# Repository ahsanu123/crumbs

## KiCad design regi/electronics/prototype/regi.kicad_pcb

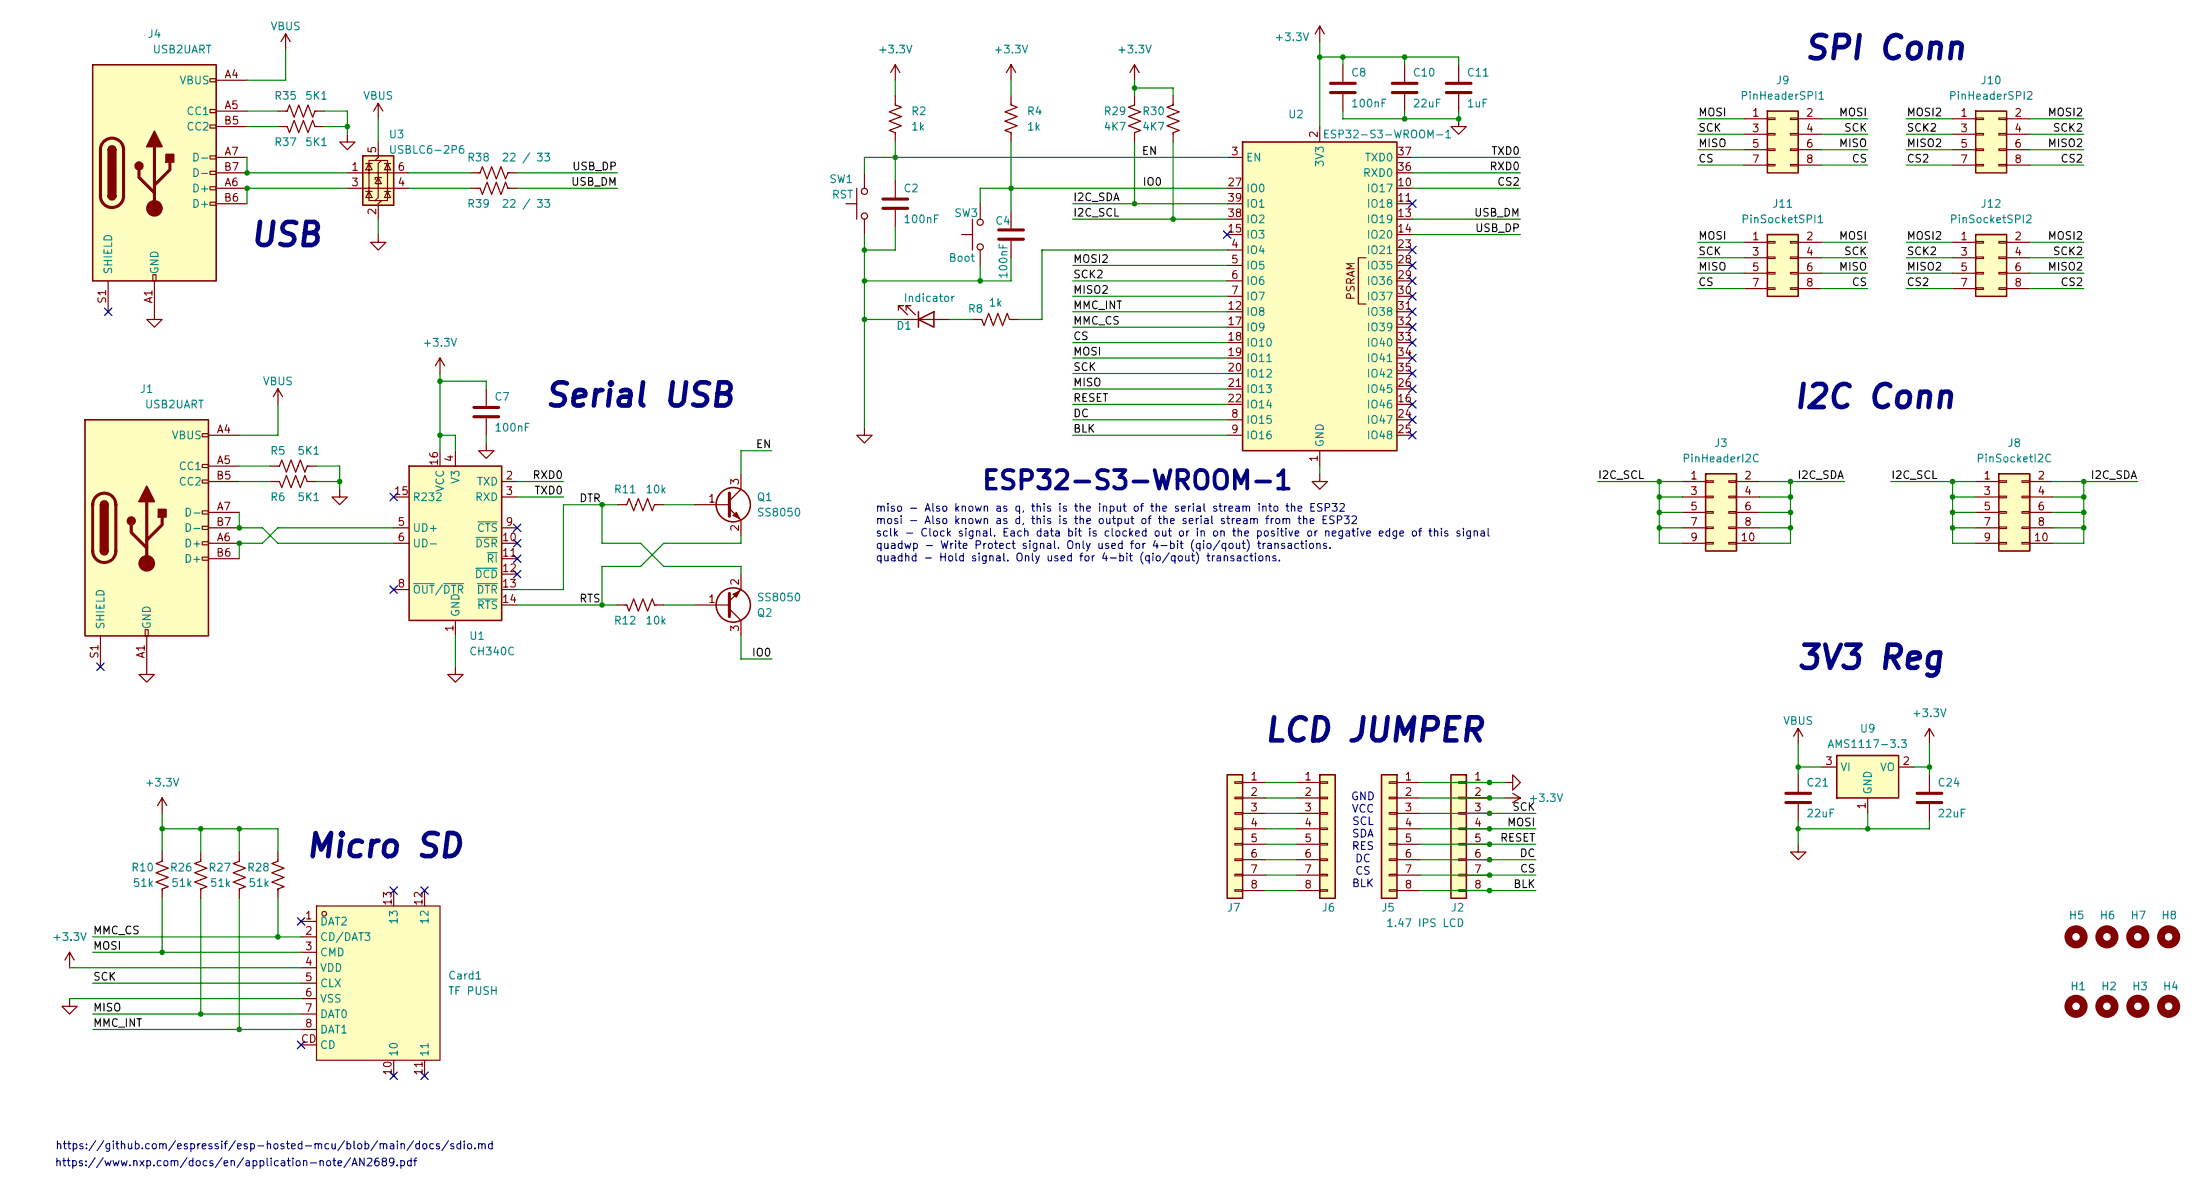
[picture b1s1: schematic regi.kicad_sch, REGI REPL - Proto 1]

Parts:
C2, C4, C7, C8: 100nF; C_0805_2012Metric_Pad1.18x1.45mm_HandSolder
C10, C21, C24: 22uF; C_0805_2012Metric_Pad1.18x1.45mm_HandSolder
C11: 1uF; C_0805_2012Metric_Pad1.18x1.45mm_HandSolder
Card1: TF PUSH; TF-SMD_TF-PUSH; MPN TF PUSH; LCSC Part C393941
D1: Indicator; LED_1206_3216Metric_Pad1.42x1.75mm_HandSolder
H1, H2, H3, H4: MountingHole; MountingHole_2mm
H5, H6, H7, H8: MountingHole; MountingHole_3.2mm_M3
J1, J4: USB2UART; USB_C_Receptacle_GCT_USB4110
J2: 1.47 IPS LCD; PinHeader_1x08_P2.54mm_Vertical
J3: PinHeaderI2C; PinHeader_2x05_P2.54mm_Vertical
J5, J6, J7: lcd jumper; PinHeader_1x08_P2.54mm_Vertical
J8: PinSocketI2C; PinSocket_2x05_P2.54mm_Vertical
J9: PinHeaderSPI1; PinHeader_2x04_P2.54mm_Vertical
J10: PinHeaderSPI2; PinHeader_2x04_P2.54mm_Vertical
J11: PinSocketSPI1; PinHeader_2x04_P2.54mm_Vertical
J12: PinSocketSPI2; PinHeader_2x04_P2.54mm_Vertical
Q1, Q2: SS8050; SOT-23_Handsoldering
R2, R4, R8: 1k; R_0805_2012Metric_Pad1.20x1.40mm_HandSolder
R5, R6, R35, R37: 5K1; R_0805_2012Metric_Pad1.20x1.40mm_HandSolder
R10, R26, R27, R28: 51k; R_0805_2012Metric_Pad1.20x1.40mm_HandSolder
R11, R12: 10k; R_0805_2012Metric_Pad1.20x1.40mm_HandSolder
R29, R30: 4K7; R_0805_2012Metric_Pad1.20x1.40mm_HandSolder
R38, R39: 22 / 33; R_0805_2012Metric_Pad1.20x1.40mm_HandSolder
SW1: RST; SW_SPST_EVQP7A
SW3: Boot; SW_SPST_EVQP7A
U1: CH340C; SOIC-16_3.9x9.9mm_P1.27mm
U2: ESP32-S3-WROOM-1
U3: USBLC6-2P6; SOT-666
U9: AMS1117-3.3; SOT-223-3_TabPin2

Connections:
+3.3V: C7.1, C8.1, C10.1, C11.1, C24.1, Card1.4 (VDD), J2.2, J5.2, R2.1, R4.1, R10.1, R26.1, R27.1, R28.1, R29.1, R30.1, U1.4 (V3), U1.16 (VCC), U2.2 (3V3), U9.2 (VO)
/BLK: J2.8, J5.8, U2.9 (IO16)
/CS: J2.7, J5.7, J9.7, J9.8, J11.7, J11.8, U2.18 (IO10)
/CS2: J10.7, J10.8, J12.7, J12.8, U2.10 (IO17)
/DC: J2.6, J5.6, U2.8 (IO15)
/DTR: Q2.2 (E), R11.2, U1.13 (~DTR)
/EN: C2.1, Q1.3 (C), R2.2, SW1.2, U2.3 (EN)
/I2C_SCL: J3.1, J3.3, J3.5, J3.7, J3.9, J8.1, J8.3, J8.5, J8.7, J8.9, R30.2, U2.38 (IO2)
/I2C_SDA: J3.2, J3.4, J3.6, J3.8, J3.10, J8.2, J8.4, J8.6, J8.8, J8.10, R29.2, U2.39 (IO1)
/IO0: C4.1, Q2.3 (C), R4.2, SW3.2, U2.27 (IO0)
/MISO: Card1.7 (DAT0), J9.5, J9.6, J11.5, J11.6, R26.2, U2.21 (IO13)
/MISO2: J10.5, J10.6, J12.5, J12.6, U2.7 (IO7)
/MMC_CS: Card1.2 (CD/DAT3), R28.2, U2.17 (IO9)
/MMC_INT: Card1.8 (DAT1), R27.2, U2.12 (IO8)
/MOSI: Card1.3 (CMD), J2.4, J5.4, J9.1, J9.2, J11.1, J11.2, R10.2, U2.19 (IO11)
/MOSI2: J10.1, J10.2, J12.1, J12.2, U2.5 (IO5)
/RESET: J2.5, J5.5, U2.22 (IO14)
/RTS: Q1.2 (E), R12.2, U1.14 (~RTS)
/RXD0: U1.2 (TXD), U2.36 (RXD0)
/SCK: Card1.5 (CLX), J2.3, J5.3, J9.3, J9.4, J11.3, J11.4, U2.20 (IO12)
/SCK2: J10.3, J10.4, J12.3, J12.4, U2.6 (IO6)
/TXD0: U1.3 (RXD), U2.37 (TXD0)
/USB_DM: R39.1, U2.13 (IO19)
/USB_DP: R38.1, U2.14 (IO20)
GND: C2.2, C4.2, C7.2, C8.2, C10.2, C11.2, C21.2, C24.2, Card1.6 (VSS), D1.1 (K), J1.A1 (GND), J1.A12 (GND), J1.B1 (GND), J1.B12 (GND), J2.1, J4.A1 (GND), J4.A12 (GND), J4.B1 (GND), J4.B12 (GND), J5.1, R5.1, R6.1, R35.1, R37.1, SW1.1, SW3.1, U1.1 (GND), U2.1 (GND), U2.40 (GND), U2.41 (GND), U3.2 (GND), U9.1 (GND)
unnamed: D1.2 (A), R8.1
unnamed: J1.A5 (CC1), R5.2
unnamed: J1.B5 (CC2), R6.2
unnamed: J4.A5 (CC1), R35.2
unnamed: J4.B5 (CC2), R37.2
unnamed: J4.A6 (D+), J4.B6 (D+), U3.3 (I/O2)
unnamed: J4.A7 (D-), J4.B7 (D-), U3.1 (I/O1)
unnamed: J6.1, J7.1
unnamed: J6.2, J7.2
unnamed: J6.3, J7.3
unnamed: J6.4, J7.4
unnamed: J6.5, J7.5
unnamed: J6.6, J7.6
unnamed: J6.7, J7.7
unnamed: J6.8, J7.8
unnamed: Q1.1 (B), R11.1
unnamed: Q2.1 (B), R12.1
unnamed: R38.2, U3.6 (I/O1)
unnamed: R39.2, U3.4 (I/O2)
unnamed: J1.A6 (D+), J1.B6 (D+), U1.5 (UD+)
unnamed: J1.A7 (D-), J1.B7 (D-), U1.6 (UD-)
unnamed: R8.2, U2.4 (IO4)
VBUS: C21.1, J1.A4 (VBUS), J1.A9 (VBUS), J1.B4 (VBUS), J1.B9 (VBUS), J4.A4 (VBUS), J4.A9 (VBUS), J4.B4 (VBUS), J4.B9 (VBUS), U3.5 (VBUS), U9.3 (VI)

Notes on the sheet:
miso - Also known as q, this is the input of the serial stream into the ESP32 mosi - Also known as d, this is the output of the serial stream from the ESP32 sclk - Clock signal. Each data bit is clocked out or in on the positive or negative edge of this signal quadwp - Write Protect signal. Only us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
GND VCC SCL SDA RES DC CS BLK
Micro SD
LCD JUMPER
SPI Conn
I2C Conn
https://www.nxp.com/docs/en/application-note/AN2689.pdf
USB
ESP32-S3-WROOM-1
Serial USB
3V3 Reg
https://github.com/espressif/esp-hosted-mcu/blob/main/docs/sdio.md

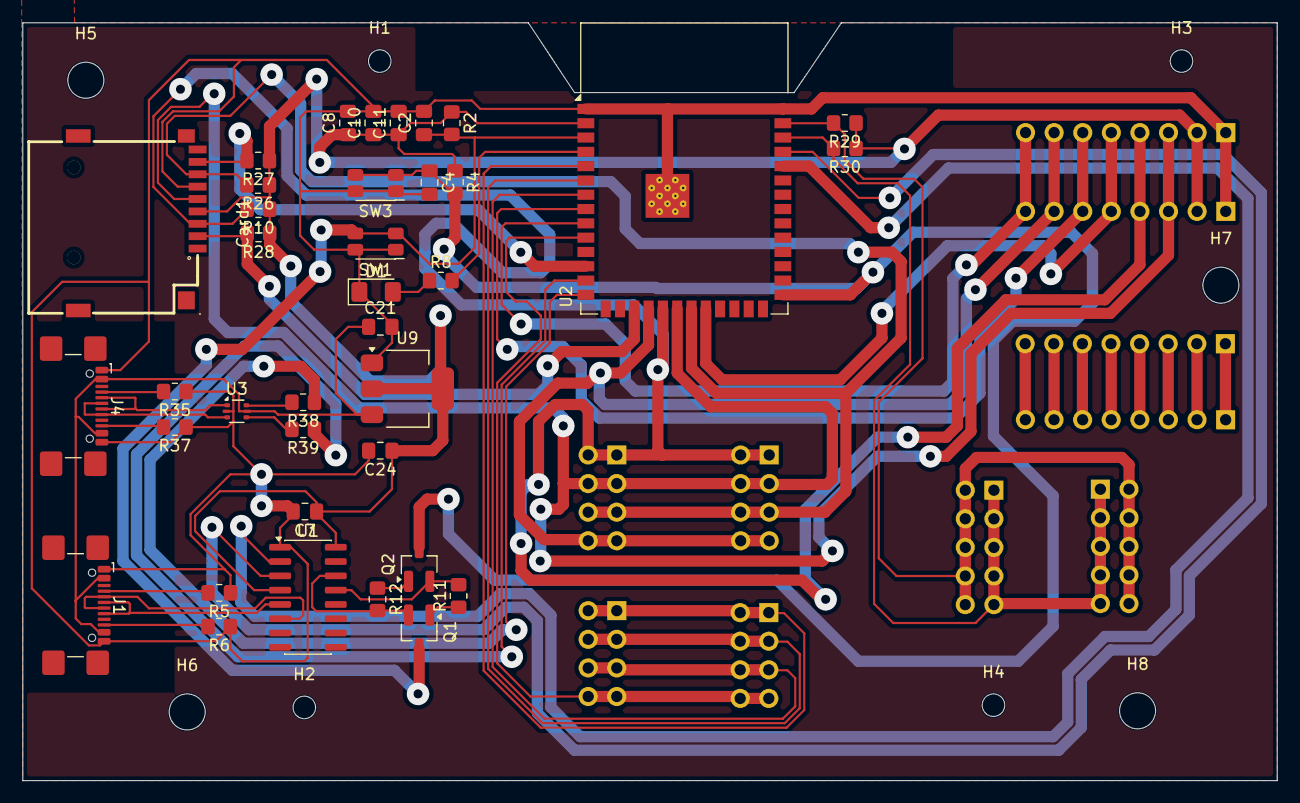
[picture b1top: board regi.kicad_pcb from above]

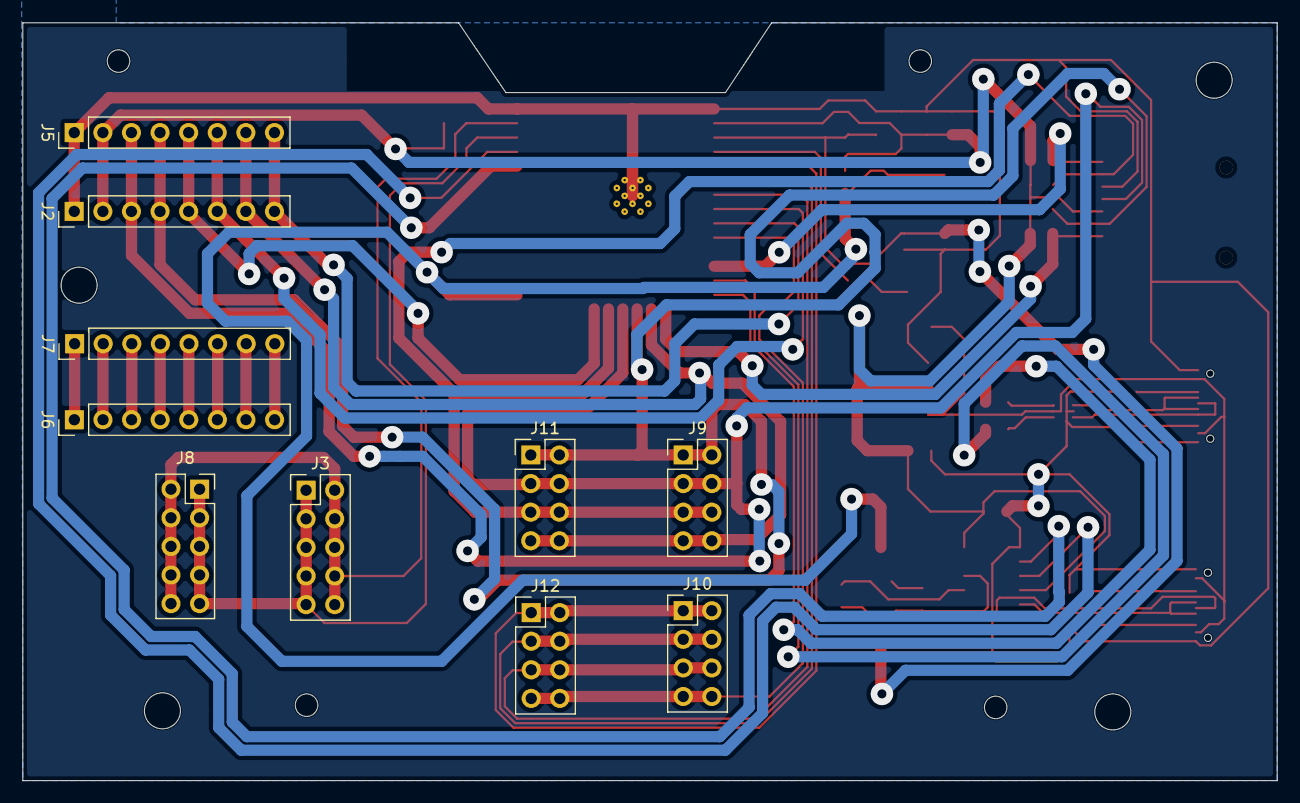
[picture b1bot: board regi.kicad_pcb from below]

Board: 2 copper layers, 111.4 x 67.3 mm, 55 parts (10 on the bottom side), 48 nets.

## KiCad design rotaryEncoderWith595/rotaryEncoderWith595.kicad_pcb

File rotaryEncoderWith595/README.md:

## Crumbs 🍪 - Rotary Encoder With 74HC595 And 74HC165

Simple Breakout Board to Learn Shift Register with Tactile Switch And Rotary Encoder 

### 🍑 Features
> 🎈 4 Rotary Encoder With Low Pass Filter Debounce  
> 🏀 4 Input  With Low Pass Filter Debounce  
> 🍨 Use 2x 74HC595  
> 🍛 Use 2x 74HC165

<sup> 27 Juni 2024 19:11 Work In Progress, Made with ♥️ by AH... </sup>

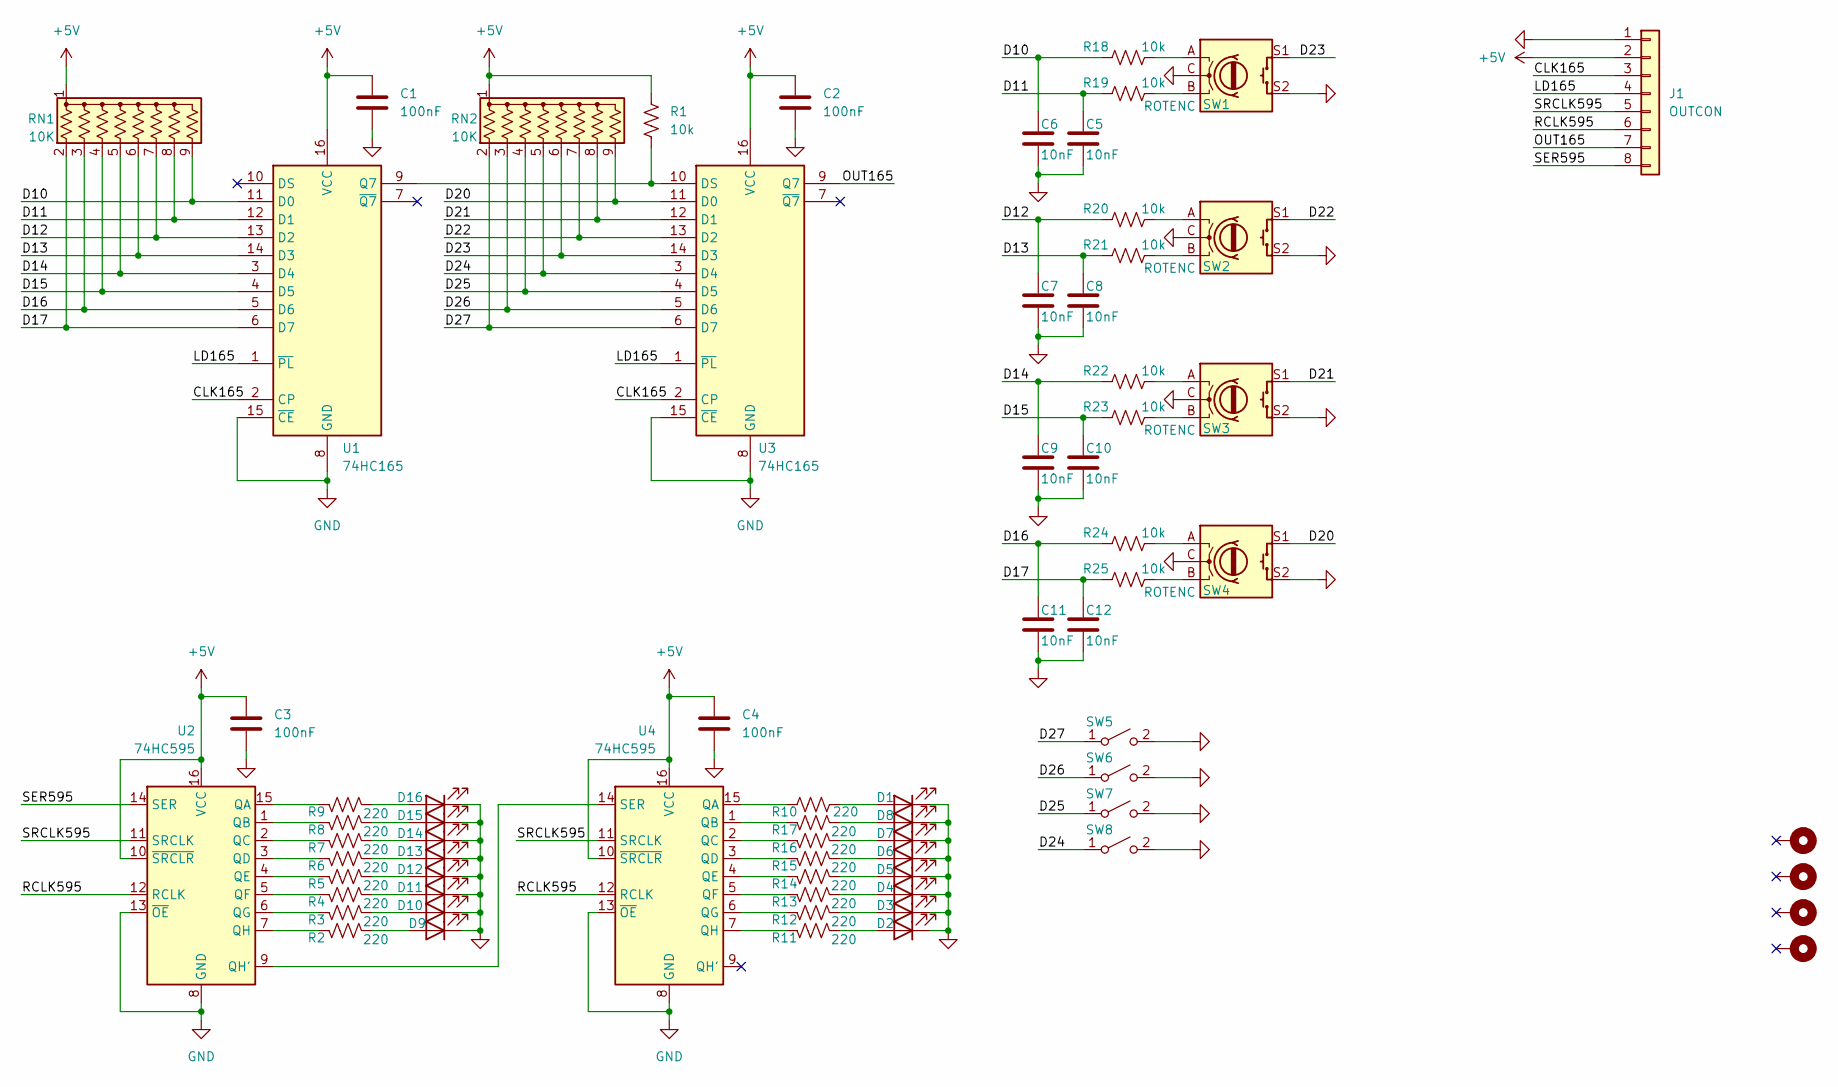
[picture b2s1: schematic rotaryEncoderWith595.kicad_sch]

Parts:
C1, C2, C3, C4: 100nF; C_Rect_L4.0mm_W2.5mm_P2.50mm
C5, C6, C7, C8, C9, C10, C11, C12: 10nF; C_Rect_L4.0mm_W2.5mm_P2.50mm
D1, D2, D3, D4, D5, D6, D7, D8, D9, D10, D11, D12, D13, D14, D15, D16: LED; LED_D3.0mm
H1, H2, H3, H4: MountingHole_Pad; MountingHole_3mm_Pad
J1: OUTCON; PinSocket_1x08_P2.54mm_Vertical
R1, R18, R19, R20, R21, R22, R23, R24, R25: 10k; R_Axial_DIN0207_L6.3mm_D2.5mm_P10.16mm_Horizontal
R2, R3, R4, R5, R6, R7, R8, R9, R10, R11, R12, R13, R14, R15, R16, R17: 220; R_Axial_DIN0207_L6.3mm_D2.5mm_P10.16mm_Horizontal
RN1, RN2: 10K; R_Array_SIP9
SW1, SW2, SW3, SW4: ROTENC; RotaryEncoder_Alps_EC11E-Switch_Vertical_H20mm
SW5, SW6, SW7, SW8: IN; SW_PUSH_6mm
U1, U3: 74HC165; DIP-16_W7.62mm_LongPads
U2, U4: 74HC595; DIP-16_W7.62mm_LongPads

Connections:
+5V: C1.1, C2.1, C3.1, C4.1, J1.2, R1.1, RN1.1 (common), RN2.1 (common), U1.16 (VCC), U2.10 (~SRCLR), U2.16 (VCC), U3.16 (VCC), U4.10 (~SRCLR), U4.16 (VCC)
/CLK165: J1.3, U1.2 (CP), U3.2 (CP)
/D10: C6.1, R18.1, RN1.9 (R8), U1.11 (D0)
/D11: C5.1, R19.1, RN1.8 (R7), U1.12 (D1)
/D12: C7.1, R20.1, RN1.7 (R6), U1.13 (D2)
/D13: C8.1, R21.1, RN1.6 (R5), U1.14 (D3)
/D14: C9.1, R22.1, RN1.5 (R4), U1.3 (D4)
/D15: C10.1, R23.1, RN1.4 (R3), U1.4 (D5)
/D16: C11.1, R24.1, RN1.3 (R2), U1.5 (D6)
/D17: C12.1, R25.1, RN1.2 (R1), U1.6 (D7)
/D20: RN2.9 (R8), SW4.S1, U3.11 (D0)
/D21: RN2.8 (R7), SW3.S1, U3.12 (D1)
/D22: RN2.7 (R6), SW2.S1, U3.13 (D2)
/D23: RN2.6 (R5), SW1.S1, U3.14 (D3)
/D24: RN2.5 (R4), SW8.1 (A), U3.3 (D4)
/D25: RN2.4 (R3), SW7.1 (A), U3.4 (D5)
/D26: RN2.3 (R2), SW6.1 (A), U3.5 (D6)
/D27: RN2.2 (R1), SW5.1 (A), U3.6 (D7)
/LD165: J1.4, U1.1 (~PL), U3.1 (~PL)
/OUT165: J1.7, U3.9 (Q7)
/RCLK595: J1.6, U2.12 (RCLK), U4.12 (RCLK)
/SER595: J1.8, U2.14 (SER)
/SRCLK595: J1.5, U2.11 (SRCLK), U4.11 (SRCLK)
GND: C1.2, C2.2, C3.2, C4.2, C5.2, C6.2, C7.2, C8.2, C9.2, C10.2, C11.2, C12.2, D1.1 (K), D2.1 (K), D3.1 (K), D4.1 (K), D5.1 (K), D6.1 (K), D7.1 (K), D8.1 (K), D9.1 (K), D10.1 (K), D11.1 (K), D12.1 (K), D13.1 (K), D14.1 (K), D15.1 (K), D16.1 (K), J1.1, SW1.C, SW1.S2, SW2.C, SW2.S2, SW3.C, SW3.S2, SW4.C, SW4.S2, SW5.2 (B), SW6.2 (B), SW7.2 (B), SW8.2 (B), U1.8 (GND), U1.15 (~CE), U2.8 (GND), U2.13 (~OE), U3.8 (GND), U3.15 (~CE), U4.8 (GND), U4.13 (~OE)
unnamed: D1.2 (A), R10.2
unnamed: D2.2 (A), R11.2
unnamed: D3.2 (A), R12.2
unnamed: D4.2 (A), R13.2
unnamed: D5.2 (A), R14.2
unnamed: D6.2 (A), R15.2
unnamed: D7.2 (A), R16.2
unnamed: D8.2 (A), R17.2
unnamed: D9.2 (A), R2.2
unnamed: D10.2 (A), R3.2
unnamed: D11.2 (A), R4.2
unnamed: D12.2 (A), R5.2
unnamed: D13.2 (A), R6.2
unnamed: D14.2 (A), R7.2
unnamed: D15.2 (A), R8.2
unnamed: D16.2 (A), R9.2
unnamed: R18.2, SW1.A
unnamed: R19.2, SW1.B
unnamed: R20.2, SW2.A
unnamed: R21.2, SW2.B
unnamed: R22.2, SW3.A
unnamed: R23.2, SW3.B
unnamed: R24.2, SW4.A
unnamed: R25.2, SW4.B
unnamed: R1.2, U1.9 (Q7), U3.10 (DS)
unnamed: R9.1, U2.15 (QA)
unnamed: R8.1, U2.1 (QB)
unnamed: R7.1, U2.2 (QC)
unnamed: R6.1, U2.3 (QD)
unnamed: R5.1, U2.4 (QE)
unnamed: R4.1, U2.5 (QF)
unnamed: R3.1, U2.6 (QG)
unnamed: U2.9 (QH'), U4.14 (SER)
unnamed: R2.1, U2.7 (QH)
unnamed: R10.1, U4.15 (QA)
unnamed: R17.1, U4.1 (QB)
unnamed: R16.1, U4.2 (QC)
unnamed: R15.1, U4.3 (QD)
unnamed: R14.1, U4.4 (QE)
unnamed: R13.1, U4.5 (QF)
unnamed: R12.1, U4.6 (QG)
unnamed: R11.1, U4.7 (QH)

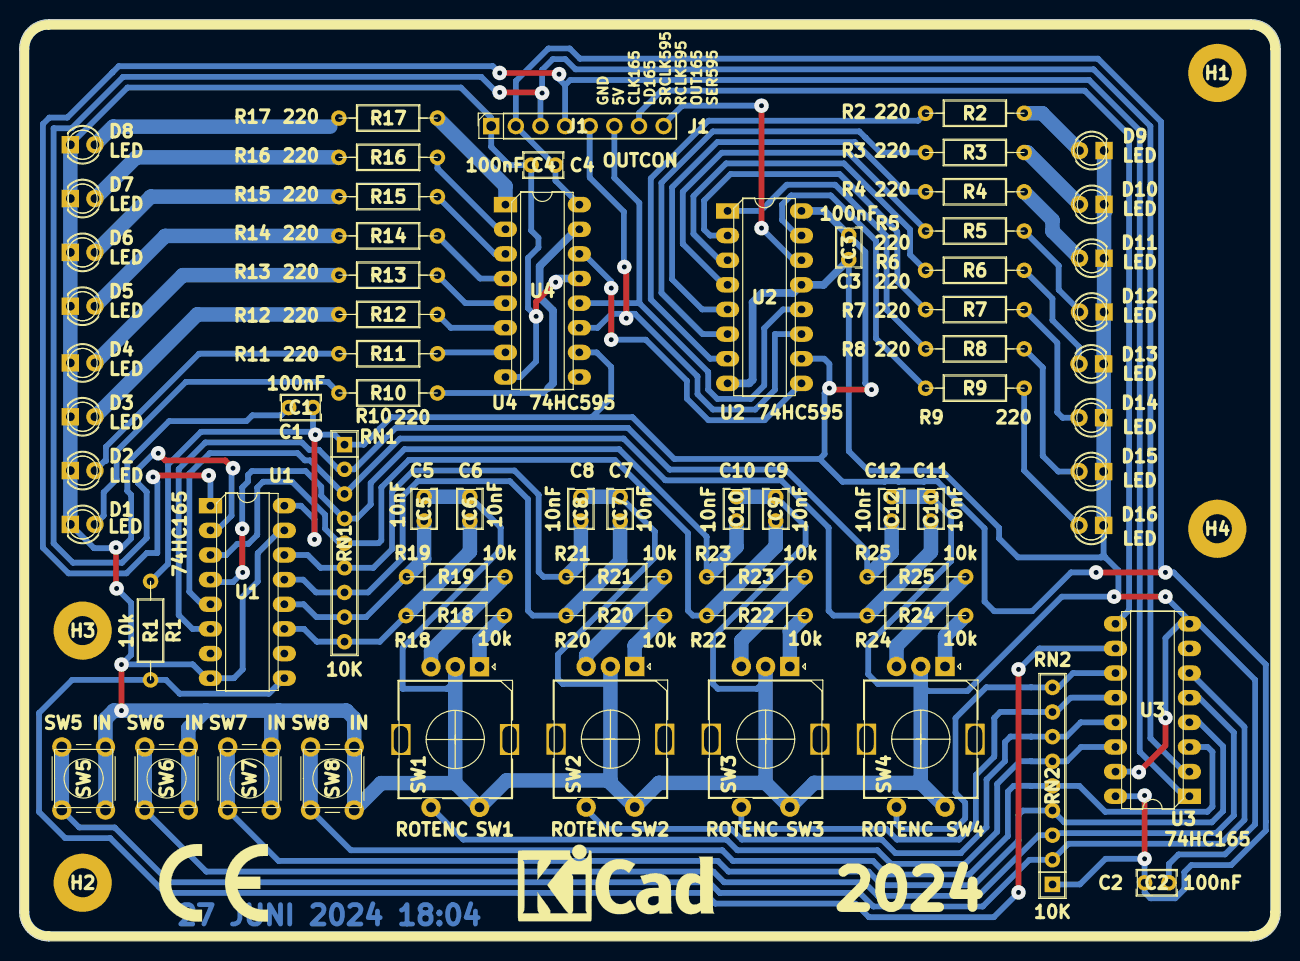
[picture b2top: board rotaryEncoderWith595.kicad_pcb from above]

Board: 2 copper layers, 130.0 x 95.0 mm, 72 parts (0 on the bottom side), 66 nets.

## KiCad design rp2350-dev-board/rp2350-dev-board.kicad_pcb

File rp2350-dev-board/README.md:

# introduction 

## References 

- https://www.solder.party/docs/rp2350-stamp/
- https://www.solder.party/docs/rp2xxx-stamp-carrier-xl/
- https://datasheets.raspberrypi.com/rp2350/hardware-design-with-rp2350.pdf
- https://cdn-learn.adafruit.com/assets/assets/000/132/211/original/adafruit_products_schem.png?1725912286
- https://datasheets.raspberrypi.com/rp2350/rp2350-datasheet.pdf

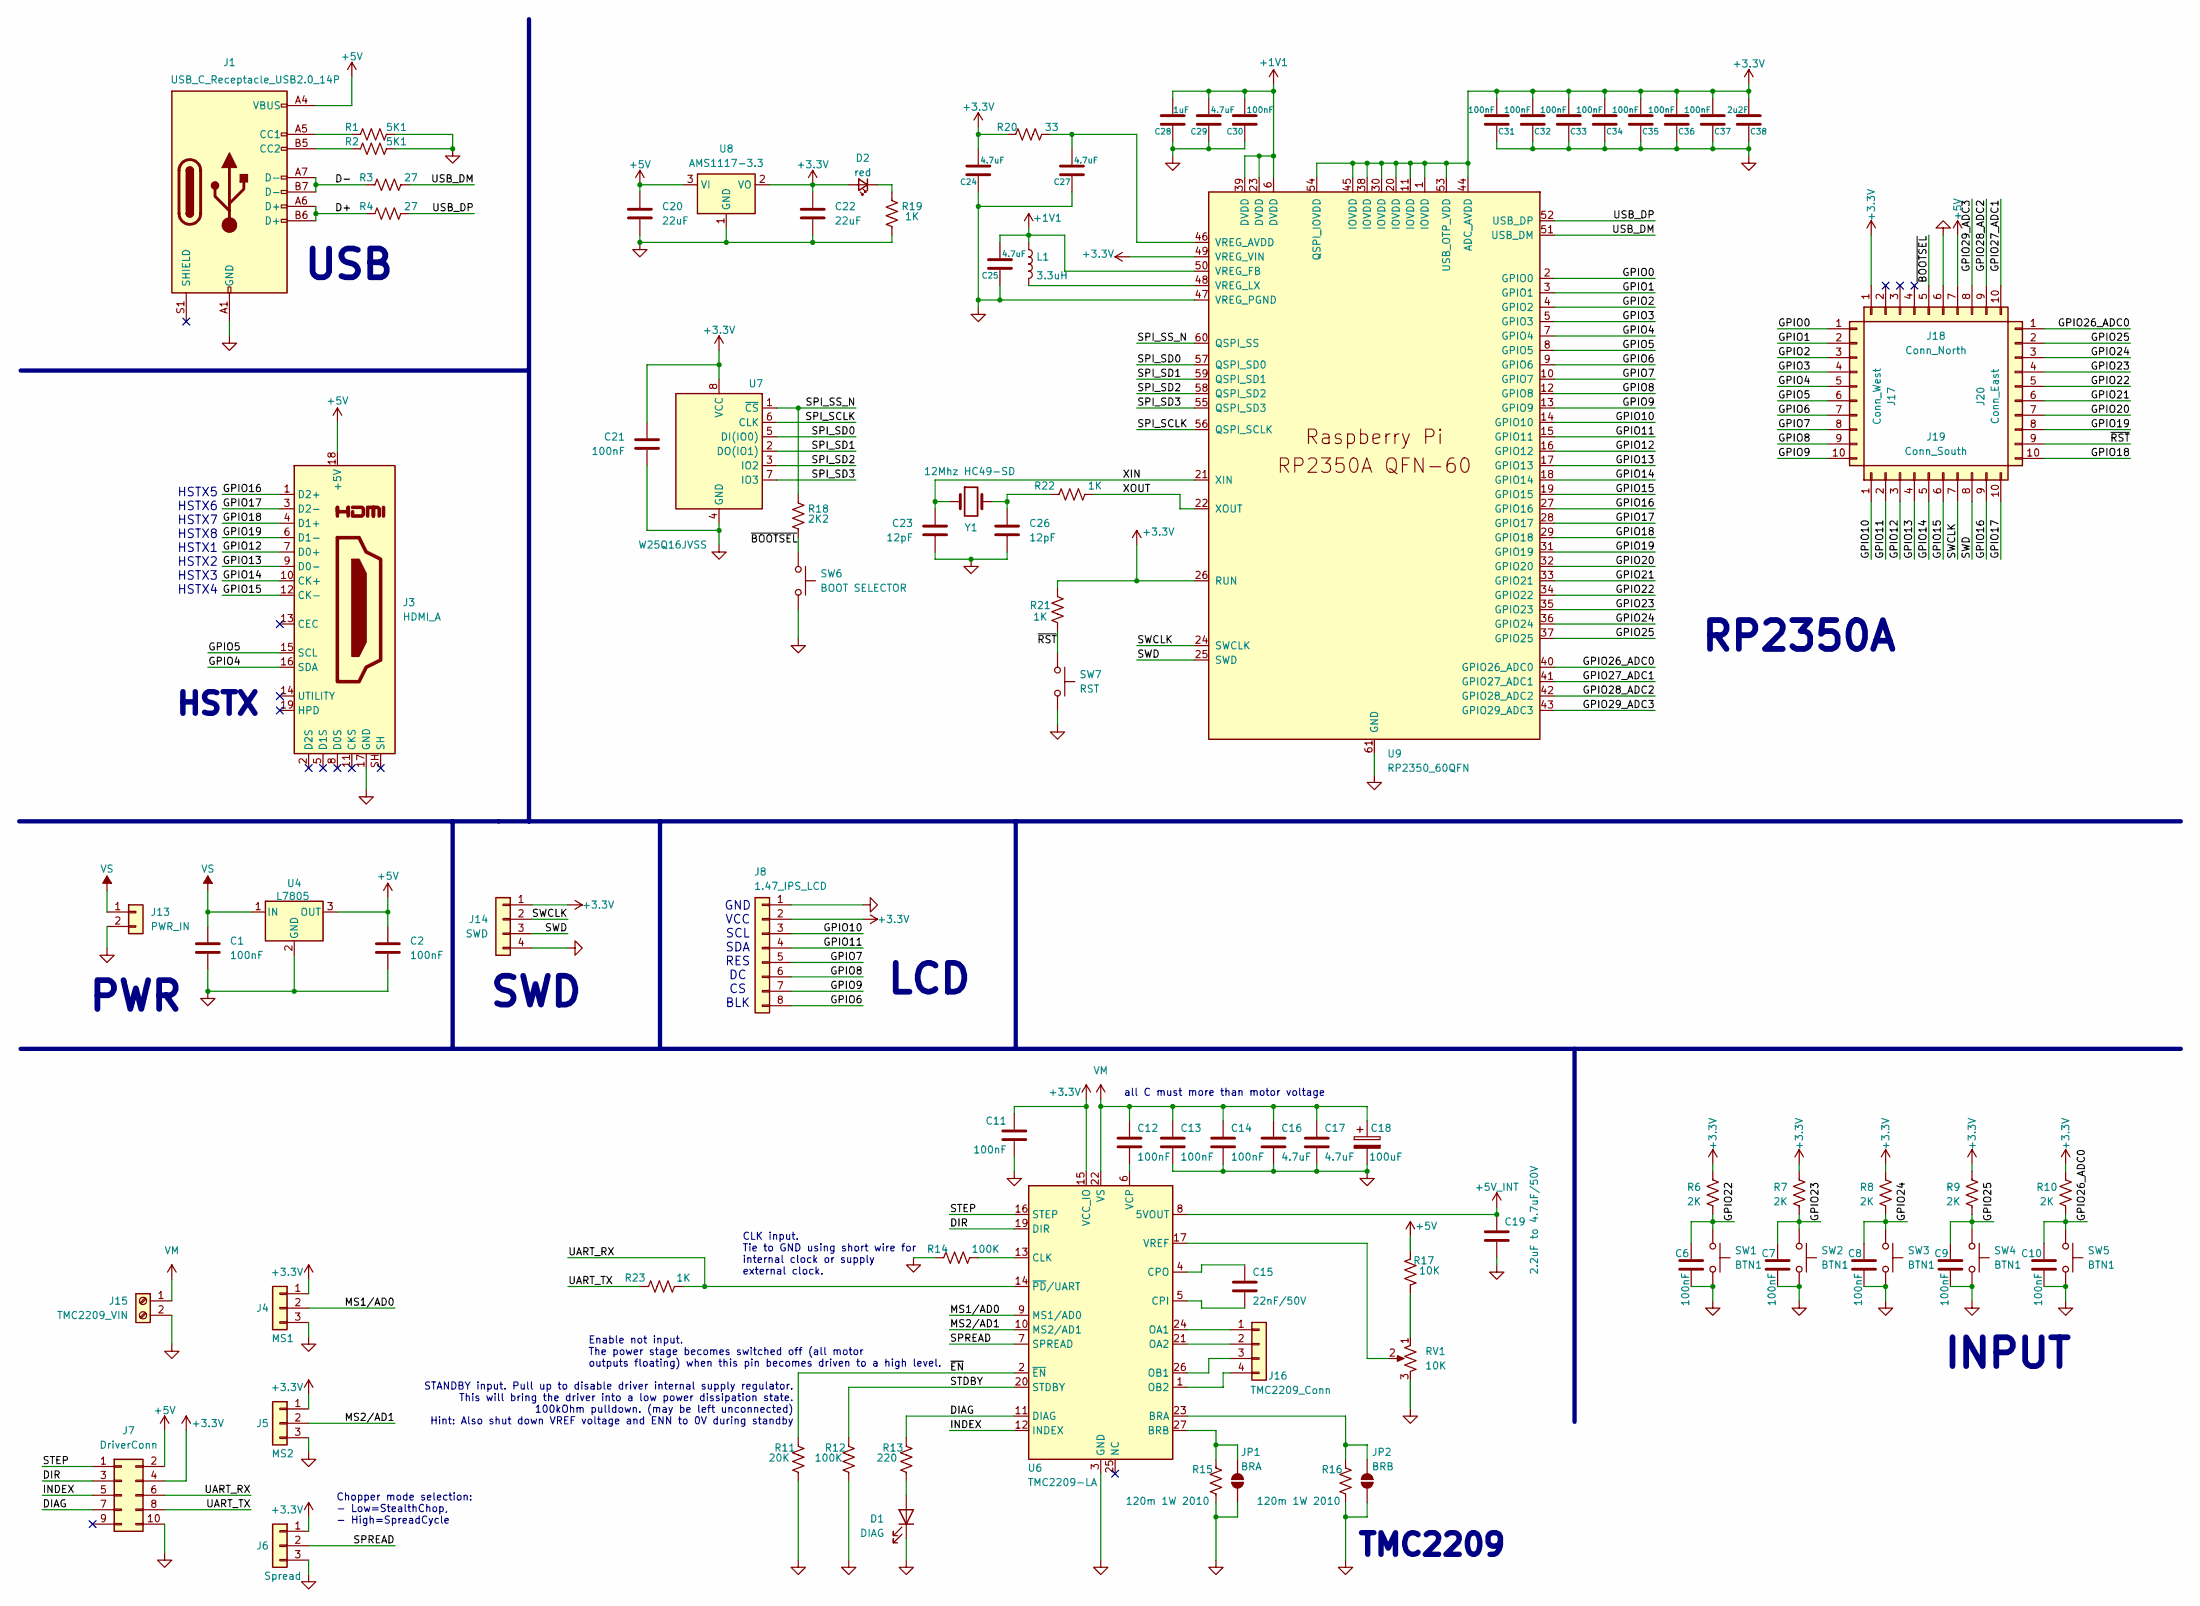
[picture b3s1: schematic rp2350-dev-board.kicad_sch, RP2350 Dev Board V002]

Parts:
C1, C2, C6, C7, C8, C9, C10, C11, C12, C13, C14: 100nF; C_0805_2012Metric_Pad1.18x1.45mm_HandSolder
C15: 22nF/50V; C_0805_2012Metric_Pad1.18x1.45mm_HandSolder
C16, C17: 4.7uF; C_0805_2012Metric_Pad1.18x1.45mm_HandSolder
C18: 100uF; CP_Radial_D8.0mm_P3.50mm
C19: 2.2uF to 4.7uF/50V; C_0805_2012Metric_Pad1.18x1.45mm_HandSolder
C20, C22: 22uF; C_0603_1608Metric_Pad1.08x0.95mm_HandSolder
C21, C30, C31, C32, C33, C34, C35, C36, C37: 100nF; C_0603_1608Metric_Pad1.08x0.95mm_HandSolder
C23, C26: 12pF; C_0603_1608Metric_Pad1.08x0.95mm_HandSolder
C24, C25, C27, C29: 4.7uF; C_0603_1608Metric_Pad1.08x0.95mm_HandSolder
C28: 1uF; C_0603_1608Metric_Pad1.08x0.95mm_HandSolder
C38: 2u2F; C_0603_1608Metric_Pad1.08x0.95mm_HandSolder
D1: DIAG; LED_0805_2012Metric_Pad1.15x1.40mm_HandSolder
D2: red; LED_0805_2012Metric_Pad1.15x1.40mm_HandSolder; mouser# 78-VLMS1300-GS08
J1: USB_C_Receptacle_USB2.0_14P; USB_C_Receptacle_GCT_USB4110
J3: HDMI_A; HDMI_A_Molex_208658-1001_Horizontal
J4: MS1; PinHeader_1x03_P2.54mm_Vertical
J5: MS2; PinHeader_1x03_P2.54mm_Vertical
J6: Spread; PinHeader_1x03_P2.54mm_Vertical
J7: DriverConn; IDC-Header_2x05_P2.54mm_Vertical
J8: 1.47_IPS_LCD; PinHeader_1x08_P2.54mm_Vertical
J13: PWR_IN; Hirose_DF13-02P-1.25DSA_1x02_P1.25mm_Vertical
J14: SWD; Molex_Micro-Latch_53253-0470_1x04_P2.00mm_Vertical
J15: TMC2209_VIN; TerminalBlock_Phoenix_PT-1,5-2-5.0-H_1x02_P5.00mm_Horizontal
J16: TMC2209_Conn; Molex_Nano-Fit_105313-xx04_1x04_P2.50mm_Horizontal
J17: Conn_West; PinHeader_1x10_P2.54mm_Vertical
J18: Conn_North; PinHeader_1x10_P2.54mm_Vertical
J19: Conn_South; PinHeader_1x10_P2.54mm_Vertical
J20: Conn_East; PinHeader_1x10_P2.54mm_Vertical
JP1: BRA; SolderJumper-2_P1.3mm_Open_RoundedPad1.0x1.5mm
JP2: BRB; SolderJumper-2_P1.3mm_Open_RoundedPad1.0x1.5mm
L1: 3.3uH; L_0805_2012Metric_Pad1.05x1.20mm_HandSolder
R1, R2: 5K1; R_0805_2012Metric_Pad1.20x1.40mm_HandSolder
R3, R4: 27; R_0805_2012Metric_Pad1.20x1.40mm_HandSolder
R6, R7, R8, R9, R10: 2K; R_0805_2012Metric_Pad1.20x1.40mm_HandSolder
R11: 20K; R_0805_2012Metric_Pad1.20x1.40mm_HandSolder
R12, R14: 100K; R_0805_2012Metric_Pad1.20x1.40mm_HandSolder
R13: 220; R_0805_2012Metric_Pad1.20x1.40mm_HandSolder
R15, R16: 120m 1W 2010; R_2010_5025Metric
R17: 10K; R_0805_2012Metric_Pad1.20x1.40mm_HandSolder
R18: 2K2; R_0805_2012Metric_Pad1.20x1.40mm_HandSolder
R19, R21, R22, R23: 1K; R_0805_2012Metric_Pad1.20x1.40mm_HandSolder
R20: 33; R_0805_2012Metric_Pad1.20x1.40mm_HandSolder
RV1: 10K; Potentiometer_Bourns_3269W_Vertical
SW1, SW2, SW3, SW4, SW5: BTN1; SW_Push_1P1T_NO_6x6mm_H9.5mm
SW6: BOOT SELECTOR; SW_Push_1P1T_NO_CK_KMR2
SW7: RST; SW_Push_1P1T_NO_CK_KMR2
U4: L7805; TO-220-3_Horizontal_TabDown
U6: TMC2209-LA; VQFN-28-1EP_5x5mm_P0.5mm_EP3.7x3.7mm
U7: W25Q16JVSS; SOIC-8_5.3x5.3mm_P1.27mm
U8: AMS1117-3.3; SOT-223-3_TabPin2
U9: RP2350_60QFN; RP2350-QFN-60-1EP_7x7_P0.4mm_EP3.4x3.4mm_ThermalVias
Y1: 12Mhz HC49-SD; Crystal_SMD_HC49-SD

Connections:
+1V1: C25.1, C28.1, C29.1, C30.1, L1.1, U9.6 (DVDD), U9.23 (DVDD), U9.39 (DVDD), U9.50 (VREG_FB)
+3.3V: C11.1, C21.1, C22.1, C24.1, C31.1, C32.1, C33.1, C34.1, C35.1, C36.1, C37.1, C38.1, D2.2 (A), J4.1, J5.1, J6.1, J7.4, J8.2, J14.1, J18.1, R6.2, R7.2, R8.2, R9.2, R10.2, R20.1, R21.2, U6.15 (VCC_IO), U7.8 (VCC), U8.2 (VO), U9.1 (IOVDD), U9.11 (IOVDD), U9.20 (IOVDD), U9.26 (RUN), U9.30 (IOVDD), U9.38 (IOVDD), U9.44 (ADC_AVDD), U9.45 (IOVDD), U9.49 (VREG_VIN), U9.53 (USB_OTP_VDD), U9.54 (QSPI_IOVDD)
+5V: C2.1, C20.1, J1.A4 (VBUS), J1.A9 (VBUS), J1.B4 (VBUS), J1.B9 (VBUS), J3.18 (+5V), J7.2, J18.7, R17.1, U4.3 (OUT), U8.3 (VI)
+5V_INT: C19.1, U6.8 (5VOUT)
/D+: J1.A6 (D+), J1.B6 (D+), R4.1
/D-: J1.A7 (D-), J1.B7 (D-), R3.1
/DIAG: J7.7, R13.1, U6.11 (DIAG)
/DIR: J7.3, U6.19 (DIR)
/GPIO0: J17.1, U9.2 (GPIO0)
/GPIO1: J17.2, U9.3 (GPIO1)
/GPIO2: J17.3, U9.4 (GPIO2)
/GPIO3: J17.4, U9.5 (GPIO3)
/GPIO4: J3.16 (SDA), J17.5, U9.7 (GPIO4)
/GPIO5: J3.15 (SCL), J17.6, U9.8 (GPIO5)
/GPIO6: J8.8, J17.7, U9.9 (GPIO6)
/GPIO7: J8.5, J17.8, U9.10 (GPIO7)
/GPIO8: J8.6, J17.9, U9.12 (GPIO8)
/GPIO9: J8.7, J17.10, U9.13 (GPIO9)
/GPIO10: J8.3, J19.1, U9.14 (GPIO10)
/GPIO11: J8.4, J19.2, U9.15 (GPIO11)
/GPIO12: J3.7 (D0+), J19.3, U9.16 (GPIO12)
/GPIO13: J3.9 (D0-), J19.4, U9.17 (GPIO13)
/GPIO14: J3.10 (CK+), J19.5, U9.18 (GPIO14)
/GPIO15: J3.12 (CK-), J19.6, U9.19 (GPIO15)
/GPIO16: J3.1 (D2+), J19.9, U9.27 (GPIO16)
/GPIO17: J3.3 (D2-), J19.10, U9.28 (GPIO17)
/GPIO18: J3.4 (D1+), J20.10, U9.29 (GPIO18)
/GPIO19: J3.6 (D1-), J20.8, U9.31 (GPIO19)
/GPIO20: J20.7, U9.32 (GPIO20)
/GPIO21: J20.6, U9.33 (GPIO21)
/GPIO22: C6.1, J20.5, R6.1, SW1.1, U9.34 (GPIO22)
/GPIO23: C7.1, J20.4, R7.1, SW2.1, U9.35 (GPIO23)
/GPIO24: C8.1, J20.3, R8.1, SW3.1, U9.36 (GPIO24)
/GPIO25: C9.1, J20.2, R9.1, SW4.1, U9.37 (GPIO25)
/GPIO26_ADC0: C10.1, J20.1, R10.1, SW5.1, U9.40 (GPIO26_ADC0)
/GPIO27_ADC1: J18.10, U9.41 (GPIO27_ADC1)
/GPIO28_ADC2: J18.9, U9.42 (GPIO28_ADC2)
/GPIO29_ADC3: J18.8, U9.43 (GPIO29_ADC3)
/INDEX: J7.5, U6.12 (INDEX)
/MS1/AD0: J4.2, U6.9 (MS1/AD0)
/MS2/AD1: J5.2, U6.10 (MS2/AD1)
/SPI_SCLK: U7.6 (CLK), U9.56 (QSPI_SCLK)
/SPI_SD0: U7.5 (DI(IO0)), U9.57 (QSPI_SD0)
/SPI_SD1: U7.2 (DO(IO1)), U9.59 (QSPI_SD1)
/SPI_SD2: U7.3 (IO2), U9.58 (QSPI_SD2)
/SPI_SD3: U7.7 (IO3), U9.55 (QSPI_SD3)
/SPI_SS_N: R18.1, U7.1 (~CS), U9.60 (QSPI_SS)
/SPREAD: J6.2, U6.7 (SPREAD)
/STDBY: R12.1, U6.20 (STDBY)
/STEP: J7.1, U6.16 (STEP)
/SWCLK: J14.2, J19.7, U9.24 (SWCLK)
/SWD: J14.3, J19.8, U9.25 (SWD)
/UART_RX: J7.6, R23.1, U6.14 (~PD/UART)
/UART_TX: J7.8, R23.2
/USB_DM: R3.2, U9.51 (USB_DM)
/USB_DP: R4.2, U9.52 (USB_DP)
/XIN: C23.1, U9.21 (XIN), Y1.1
/XOUT: R22.2, U9.22 (XOUT)
/~BOOTSEL: J18.5, R18.2, SW6.1
/~EN: R11.1, U6.2 (~EN)
/~RST: J20.9, R21.1, SW7.1
GND: C1.2, C2.2, C6.2, C7.2, C8.2, C9.2, C10.2, C11.2, C13.2, C14.2, C16.2, C17.2, C18.2, C19.2, C20.2, C21.2, C22.2, C23.2, C24.2, C25.2, C26.2, C27.2, C28.2, C29.2, C30.2, C31.2, C32.2, C33.2, C34.2, C35.2, C36.2, C37.2, C38.2, D1.1 (K), J1.A1 (GND), J1.A12 (GND), J1.B1 (GND), J1.B12 (GND), J3.17 (GND), J4.3, J5.3, J6.3, J7.10, J8.1, J13.2, J14.4, J15.2, J18.6, JP1.1 (A), JP2.1 (A), R1.2, R2.2, R11.2, R12.2, R14.2, R15.2, R16.2, R19.2, RV1.3, SW1.2, SW2.2, SW3.2, SW4.2, SW5.2, SW6.2, SW7.2, U4.2 (GND), U6.3 (GND), U6.18 (GND), U6.29 (GND), U7.4 (GND), U8.1 (GND), U9.47 (VREG_PGND), U9.61 (GND)
unnamed: C26.1, R22.1, Y1.2
unnamed: D1.2 (A), R13.2
unnamed: D2.1 (K), R19.1
unnamed: J1.A5 (CC1), R1.1
unnamed: J1.B5 (CC2), R2.1
unnamed: J16.1, U6.24 (OA1)
unnamed: J16.2, U6.21 (OA2)
unnamed: J16.3, U6.26 (OB1)
unnamed: J16.4, U6.1 (OB2)
unnamed: JP1.2 (B), R15.1, U6.27 (BRB)
unnamed: JP2.2 (B), R16.1, U6.23 (BRA)
unnamed: R17.2, RV1.1
unnamed: R14.1, U6.13 (CLK)
unnamed: C15.2, U6.5 (CPI)
unnamed: C15.1, U6.4 (CPO)
unnamed: C12.2, U6.6 (VCP)
unnamed: RV1.2, U6.17 (VREF)
unnamed: C27.1, R20.2, U9.46 (VREG_AVDD)
unnamed: L1.2, U9.48 (VREG_LX)
VM: C12.1, C13.1, C14.1, C16.1, C17.1, C18.1, J15.1, U6.22 (VS), U6.28 (VS)
VS: C1.1, J13.1, U4.1 (IN)

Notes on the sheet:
INPUT
SWD
USB
HSTX
CLK input. Tie to GND using short wire for internal clock or supply external clock.
PWR
Chopper mode selection: - Low=StealthChop, - High=SpreadCycle
Enable not input. The power stage becomes switched off (all motor outputs floating) when this pin becomes driven to a high level.
all C must more than motor voltage
TMC2209
STANDBY input. Pull up to disable driver internal supply regulator. This will bring the driver into a low power dissipation state. 100kOhm pulldown. (may be left unconnected) Hint: Also shut down VREF voltage and ENN to 0V during standby
GND VCC SCL SDA RES DC CS BLK
RP2350A
HSTX5 HSTX6 HSTX7 HSTX8 HSTX1 HSTX2 HSTX3 HSTX4
LCD
